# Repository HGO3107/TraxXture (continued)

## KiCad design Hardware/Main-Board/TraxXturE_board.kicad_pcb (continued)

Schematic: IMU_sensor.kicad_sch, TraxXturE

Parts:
C27, C31: 100nF X7R 16V; C_0402_1005Metric
C28: 2.2nF X7R 16V; C_0402_1005Metric
JP1: jumper; SolderJumper-3_P1.3mm_Bridged12_RoundedPad1.0x1.5mm
R12: 10k; R_0402_1005Metric
U5: MPU-6050; InvenSense_QFN-24_4x4mm_P0.5mm

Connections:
+3V3: C31.2, JP1.3 (B), R12.2, U5.8 (VLOGIC), U5.13 (VDD); also elsewhere on the board
/Architectural_diagram/IMU_Sensor/MPU_CPOUT: C28.2, U5.20 (CPOUT)
/Architectural_diagram/IMU_Sensor/MPU_INT: R12.1, U5.12 (INT); also elsewhere on the board
/Architectural_diagram/IMU_Sensor/MPU_REGOUT: C27.2, U5.10 (REGOUT)
/Architectural_diagram/IMU_Sensor/MPU_SCL: U5.23 (SCL); also elsewhere on the board
/Architectural_diagram/IMU_Sensor/MPU_SDA: U5.24 (SDA); also elsewhere on the board
GND: C27.1, C28.1, C31.1, JP1.1 (A), U5.1 (CLKIN), U5.11 (FSYNC), U5.18 (GND); also elsewhere on the board
unnamed: JP1.2 (C), U5.9 (AD0)

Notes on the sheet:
AD0 (HIGH): 1101001
[8] IMU CIRCUITRY
AD0 (LOW): 1101000

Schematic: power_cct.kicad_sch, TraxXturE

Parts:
BT1: 18650 holder; SolderWire-0.1sqmm_1x02_P3.6mm_D0.4mm_OD1mm
C38: 47nF; C_0402_1005Metric
C39: 4.7uF; C_0603_1608Metric
C40, C42: 1uF; C_0603_1608Metric
C41: 2.2uF; C_0402_1005Metric
C43: 10uF X7R; C_0805_2012Metric
C44: 4.7uF; C_0805_2012Metric
C45: 10uF; C_0603_1608Metric
C46, C47, C48: 10uF; C_0805_2012Metric
C49: 100nF; C_0402_1005Metric
C55: 22uF; C_0603_1608Metric
D3: APHD1608LZGCK; LED_0603_1608Metric
D5: SZMMSZ5250BT1G; D_SOD-123
J7: Conn_01x02; TE_440055-2_1x02_P2.00mm_Horizontal
L4: MDA4020-1R0M; L_Wurth_WE-LQSH-4020
L5: VLS3012CX-2R2M-1; IND_VLS3012CX-2R2M-1
Q5: MGSF1N02LT1G; SOT-23
Q7: IPD90P03P4L-04-HXY; TO-252-2
Q8: CJ3401; SOT-23
Q9, Q10: AO3400A; SOT-23
R23: 24R; R_0603_1608Metric
R24: 5mR 1% 1watt; R_0805_2012Metric
R25: 10k 1%; R_0402_1005Metric
R26: 470R; R_0402_1005Metric
R27, R28, R29: 10k; R_0402_1005Metric
R30: 100R; R_0402_1005Metric
R31: 590k; R_0402_1005Metric
R32, R47, R48: 100k; R_0402_1005Metric
R46: 1k; R_0402_1005Metric
R49: 220k; R_0402_1005Metric
R50: 330k; R_0402_1005Metric
SW1: TL3330AF260QG; SW_TL3330AF260QG
U2: bq34210-Q1; TSSOP-14_4.4x5mm_P0.65mm
U6: BQ25601; Texas_RTW_WQFN-24-1EP_4x4mm_P0.5mm_EP2.7x2.7mm_ThermalVias
U7: TPS63000; Texas_DRC0010J_ThermalVias

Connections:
+3V3: C47.2, C48.2, R31.1, U7.1 (VOUT); also elsewhere on the board
+VBATT: BT1.1 (+), C42.2, R24.2, U2.5 (REGIN), U2.10 (SRP)
+VSYS: C39.2, C46.2, D3.2 (A), L4.1, R30.2, U6.15 (SYS), U6.16 (SYS), U7.5 (VIN); also elsewhere on the board
/Architectural_diagram/IMU_Sensor/MPU_SCL: U2.2 (SCL), U6.5 (SCL); also elsewhere on the board
/Architectural_diagram/IMU_Sensor/MPU_SDA: U2.1 (SDA), U6.6 (SDA); also elsewhere on the board
/Architectural_diagram/MCU_GPIO/GPIO12: Q5.1 (G); also elsewhere on the board
/Architectural_diagram/MCU_GPIO/GPIO20: U2.14 (ALERT); also elsewhere on the board
/Architectural_diagram/MCU_GPIO/GPIO21: U6.7 (~INT); also elsewhere on the board
/Architectural_diagram/MCU_GPIO/GPIO23: U6.9 (~CE); also elsewhere on the board
/Architectural_diagram/Power_circuitry/BB_FB: R31.2, R32.1, U7.10 (FB)
/Architectural_diagram/Power_circuitry/BG_TS: R25.1, U2.12 (TS)
/Architectural_diagram/Power_circuitry/BMS_PMID: C45.2, U6.23 (PMID)
/Architectural_diagram/Power_circuitry/BMS_PSEL: R28.1, U6.2 (PSEL)
/Architectural_diagram/Power_circuitry/BMS_TS: R27.2, R29.1, U6.11 (TS)
/Architectural_diagram/Power_circuitry/P3V3_SW1: L5.1, U7.4 (L1)
/Architectural_diagram/Power_circuitry/P3V3_SW2: L5.2, U7.2 (L2)
/Architectural_diagram/Power_circuitry/PP_SW: C38.2, L4.2, U6.19 (SW), U6.20 (SW)
/Architectural_diagram/Power_circuitry/REGN: C44.2, R27.1, U6.22 (REGN)
/Architectural_diagram/Power_circuitry/Vin: J7.1, Q7.3 (D)
/Architectural_diagram/Power_circuitry/Vin_2: C40.2, D5.1 (K), Q7.2 (S), U6.1 (VAC), U6.24 (VBUS)
GND: BT1.2 (-), C39.1, C40.1, C41.1, C42.1, C43.1, C44.1, C45.1, C46.1, C47.1, C48.1, C49.1, C55.1, J7.2, Q5.2 (S), Q9.2 (S), Q10.2 (S), R25.2, R28.2, R29.2, R32.2, R46.1, U2.3 (VSS), U6.17 (GND), U6.18 (GND), U6.25 (GND), U7.3 (PGND), U7.9 (GND), U7.11 (PGND); also elsewhere on the board
unnamed: D3.1 (K), R26.2
unnamed: D5.2 (A), Q7.1 (G), R46.2
unnamed: Q5.3 (D), R23.2
unnamed: Q8.1 (G), Q9.3 (D), R47.2
unnamed: Q9.1 (G), R49.2, SW1.1
unnamed: Q10.3 (D), R48.2, SW1.2
unnamed: C55.2, Q10.1 (G), R50.2
unnamed: C38.1, U6.21 (BTST)
unnamed: R26.1, U6.4 (STAT)
unnamed: C49.2, R30.1, U7.6 (EN), U7.7 (PS/SYNC), U7.8 (VINA)
PACK+: Q8.2 (S), R23.1, R24.1, R47.1, R48.1, U2.9 (SRN)
PACK_OUT+: C43.2, Q8.3 (D), R49.1, R50.1, U6.13 (BAT), U6.14 (BAT)

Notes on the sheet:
Recommended discharge current level from Ref manual below is C/20, pg24 sub-heading 1.3.34 https://www.ti.com/lit/ug/sluube8/sluube8.pdf?ts=1735472964646
Ensure SDA, SCL, INT are pull to high(to MCU power level)
The output voltage is 3.45V, to compensate for the voltage accross the camera communication bus.
[5] POWER CIRCUITRY
PUSH-ON/OFF
7-13.5Vdc
POWERPATH, BMS
CHARGE STATUS: * ON: IN PROGRESS * OFF: CHG COMPLETE/SLEEP mode * 1Hz pulse: Fault response the pins can be disable via EN_ICH_MON[1:0] register to hide noticeable light
+3V3 BUCK-BOOST
BATTERY GUAGE

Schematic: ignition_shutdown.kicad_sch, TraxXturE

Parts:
D4: M7; D_SMA
J9: Conn_01x02; TE_440055-2_1x02_P2.00mm_Horizontal
K1: A161CS12VDC.64; RELAY_A161CS12VDC_64; PARTREV B
Q6: MMBT2222A; SOT-23
R11: 910R; R_0402_1005Metric

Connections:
+12V: D4.1 (K), K1.A2
/Architectural_diagram/Ignition_shutdown/IGN_COM: J9.2, K1.COM
/Architectural_diagram/Ignition_shutdown/IGN_DOWN: R11.1; also elsewhere on the board
/Architectural_diagram/Ignition_shutdown/IGN_NC: J9.1, K1.NC
GND: Q6.2 (E); also elsewhere on the board
unnamed: D4.2 (A), K1.A1, Q6.3 (C)
unnamed: Q6.1 (B), R11.2

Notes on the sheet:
[11] IGNITION SHUTDOWN CIRCUITRY

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
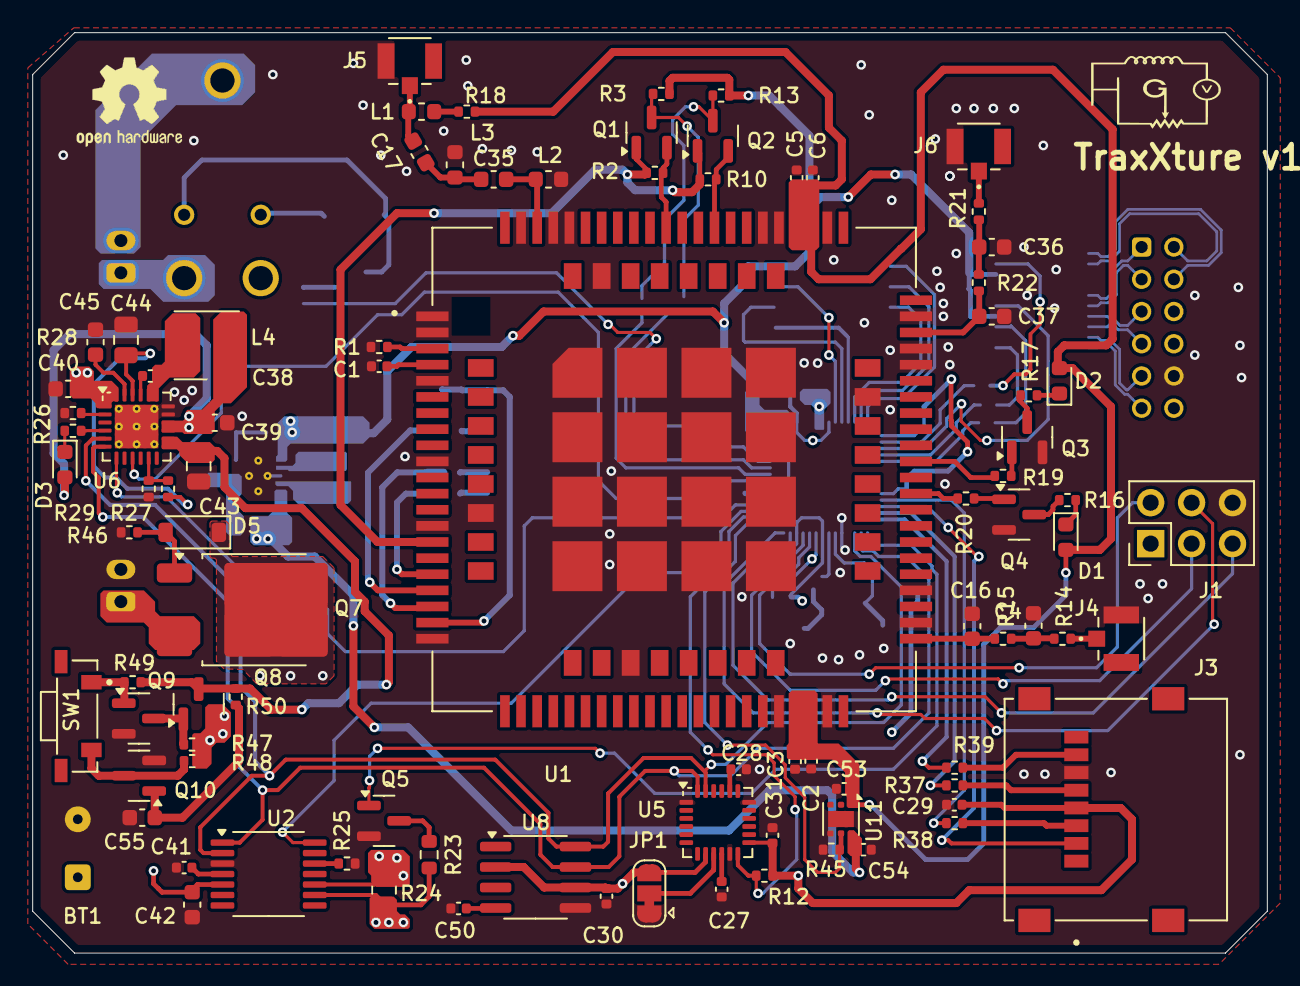
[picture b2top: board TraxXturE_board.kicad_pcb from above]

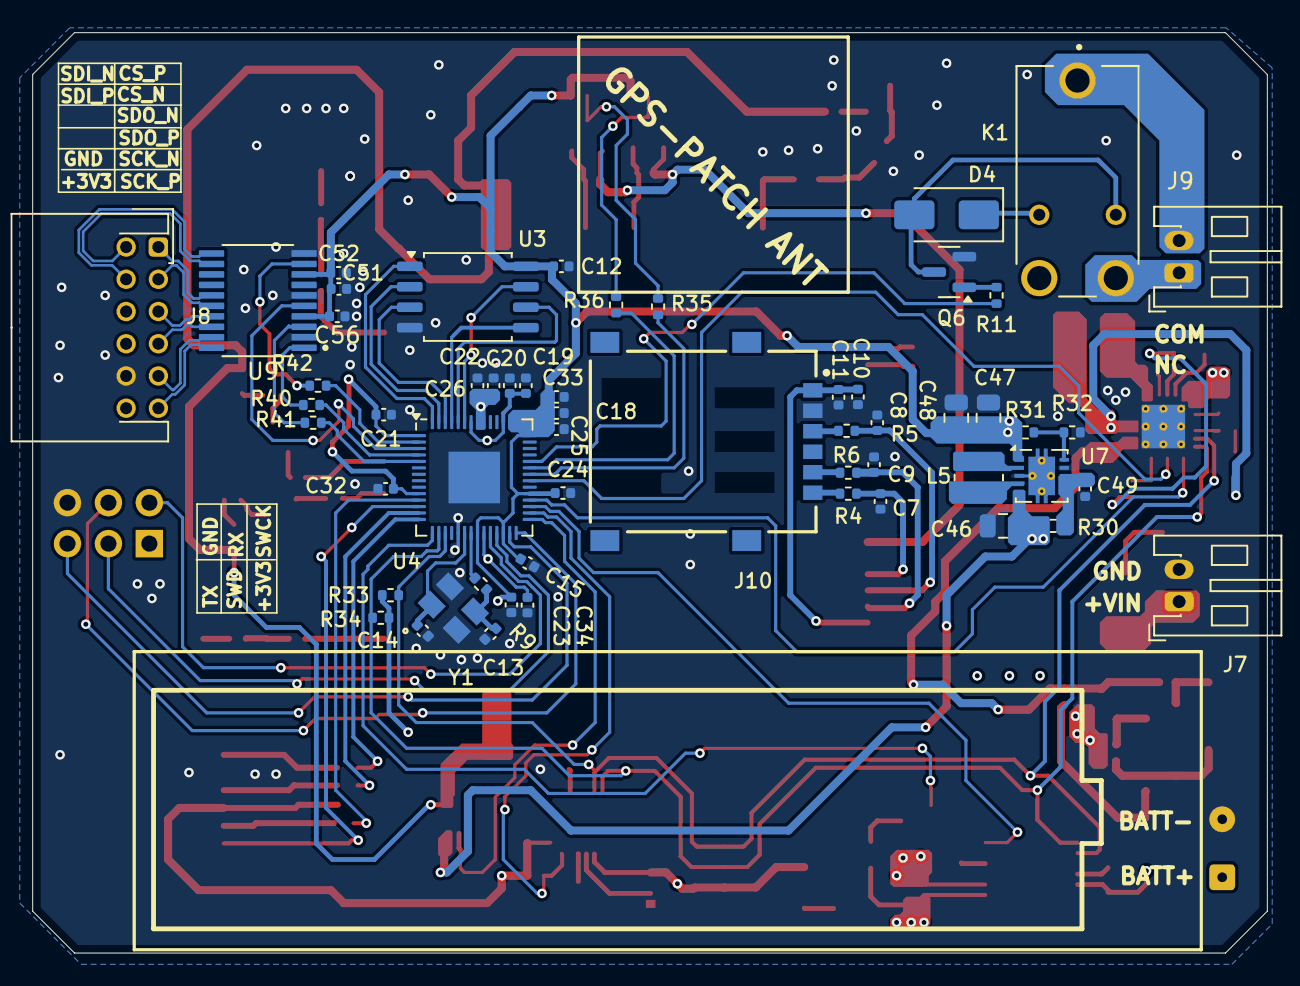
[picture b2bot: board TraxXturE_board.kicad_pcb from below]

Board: 4 copper layers, 76.6 x 57.1 mm, 146 parts (56 on the bottom side), 117 nets.

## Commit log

2025-02-06 Create .gitignore
    git ignore created
2025-02-11 Done with main board design, and camera interconnect in progress
2025-02-11 Updated the pdf for main board schematics
